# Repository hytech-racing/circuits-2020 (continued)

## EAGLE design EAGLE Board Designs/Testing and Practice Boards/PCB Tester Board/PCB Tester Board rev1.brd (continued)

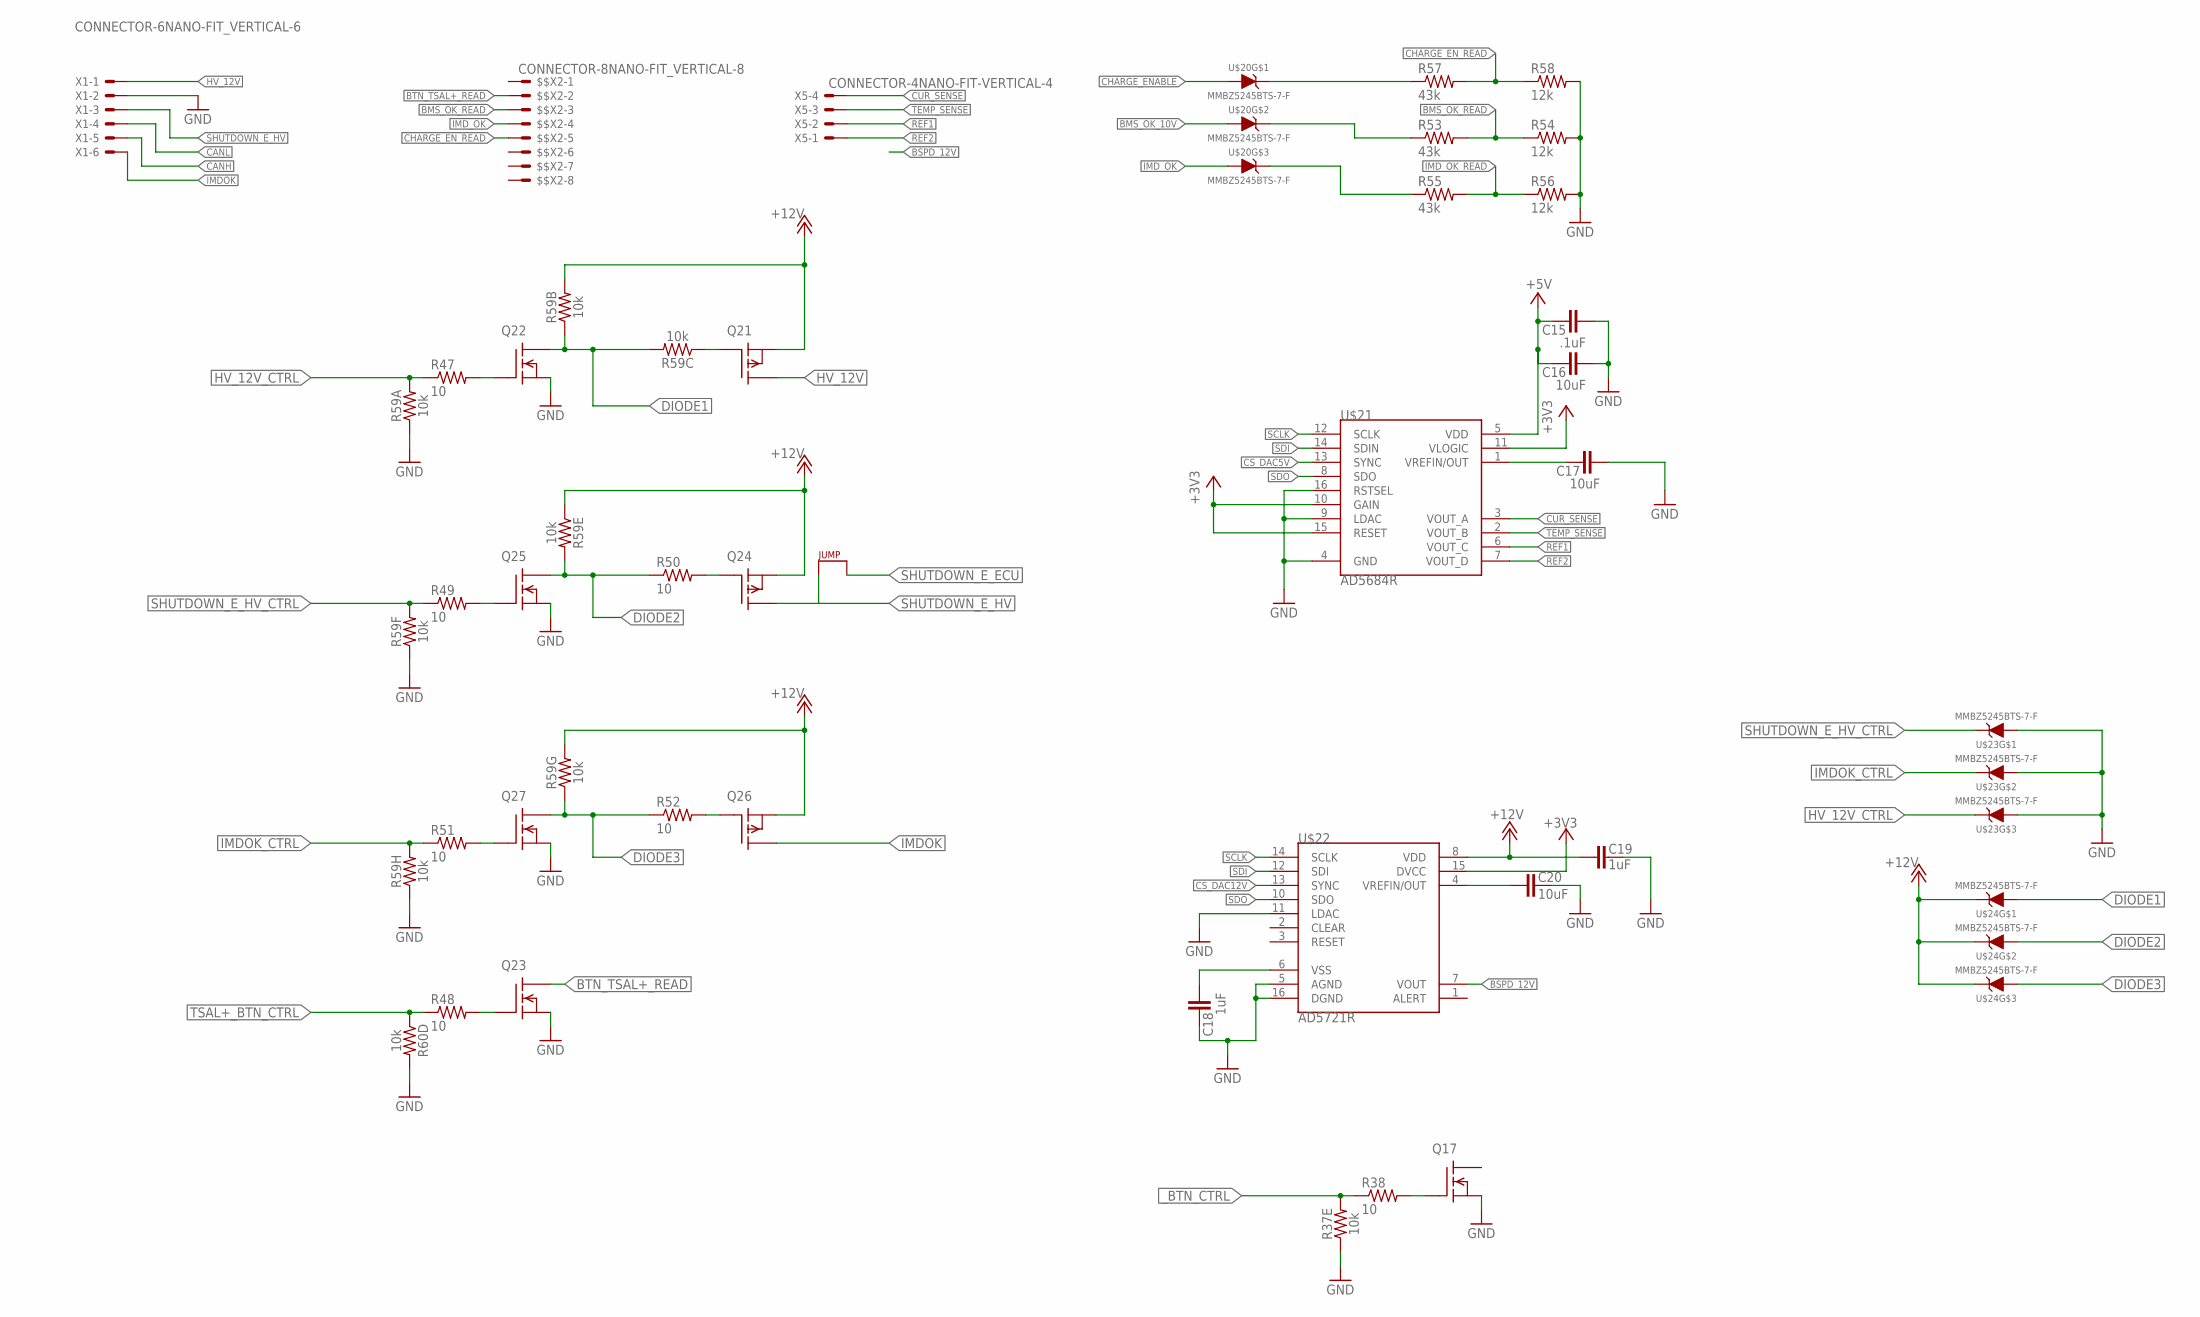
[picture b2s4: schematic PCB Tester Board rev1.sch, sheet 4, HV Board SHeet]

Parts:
$$X2: CONNECTOR-8NANO-FIT_VERTICAL-8; NANO-FIT_VERTICAL-8
C15: .1uF; 0603-CAP
C16, C17, C20: 10uF; 0603-CAP
C18, C19: 1uF; 0603-CAP
J1: JUMPER.1; 1X02
Q17, Q22, Q23, Q25, Q27: DMG3406LSOT; SOT23
Q21, Q24, Q26: P-CHANNEL_MOSFET_DMP3099L-7; SOT23
R37, R59, R60: 10k; YAG_YC248-M
R38, R47, R48, R49, R50, R51, R52: 10; 0603-RES
R53, R55, R57: 43k; 0603-RES
R54, R56, R58: 12k; 0603-RES
U$20, U$23, U$24: MMBZ5245BTS-7-F; SOT363
U$21: AD5684R; TSSOP-16
U$22: AD5721R; TSSOP-16
X1: CONNECTOR-6NANO-FIT_VERTICAL-6; NANO-FIT_VERTICAL-6
X5: CONNECTOR-4NANO-FIT-VERTICAL-4; NANO-FIT_VERTICAL-4

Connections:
+3V3: U$21.10 (GAIN), U$21.11 (VLOGIC), U$21.15 (RESET), U$22.15 (DVCC); also elsewhere on the board
+5V: C15.1, C16.1, U$21.5 (VDD); also elsewhere on the board
+12V: C19.2, Q21.2 (S), Q24.2 (S), Q26.2 (S), R59.5 (1), R59.10 (2), R59.15 (2), U$22.8 (VDD), U$24.P$4 (C), U$24.P$5 (C), U$24.P$6 (C); also elsewhere on the board
BMS_OK_10V: U$20.P$2 (A)
BMS_OK_READ: R53.2, R54.1
BSPD_12V: U$22.7 (VOUT)
BTN_TSAL+_READ: $$X2.P$2, Q23.3 (D)
CANH: X1.P$5; also elsewhere on the board
CANL: X1.P$4; also elsewhere on the board
CHARGE_ENABLE: U$20.P$1 (A)
CHARGE_EN_READ: R57.2, R58.1
CS_DAC5V: U$21.13 (SYNC); also elsewhere on the board
CS_DAC12V: U$22.13 (SYNC); also elsewhere on the board
CUR_SENSE: U$21.3 (VOUT_A), X5.P$4
DIODE1: Q22.3 (D), R59.2 (1), R59.14 (2), U$24.P$1 (A)
DIODE2: Q25.3 (D), R50.1, R59.12 (2), U$24.P$2 (A)
DIODE3: Q27.3 (D), R52.1, R59.7 (1), U$24.P$3 (A)
GND: C15.2, C16.2, C17.2, C18.1, C19.1, C20.1, Q17.2 (S), Q22.2 (S), Q23.2 (S), Q25.2 (S), Q27.2 (S), R37.5 (1), R54.2, R56.2, R58.2, R59.1, R59.6 (1), R59.8 (1), R60.13 (2), U$21.4 (GND), U$21.9 (LDAC), U$21.16 (RSTSEL), U$22.5 (AGND), U$22.11 (LDAC), U$22.16 (DGND), U$23.P$1 (A), U$23.P$2 (A), U$23.P$3 (A), X1.P$2; also elsewhere on the board
HV_12V: Q21.3 (D), X1.P$1
HV_12V_CTRL: R47.1, R59.16 (2), U$23.P$6 (C)
IMDOK: Q26.3 (D), X1.P$6
IMDOK_CTRL: R51.1, R59.9 (2), U$23.P$5 (C)
IMD_OK: U$20.P$3 (A)
IMD_OK_READ: R55.2, R56.1
unnamed: Q17.1 (G), R38.2
unnamed: Q22.1 (G), R47.2
unnamed: Q21.1 (G), R59.3 (1)
unnamed: Q23.1 (G), R48.2
unnamed: Q25.1 (G), R49.2
unnamed: Q24.1 (G), R50.2
unnamed: Q27.1 (G), R51.2
unnamed: Q26.1 (G), R52.2
unnamed: R57.1, U$20.P$4 (C)
unnamed: R53.1, U$20.P$5 (C)
unnamed: R55.1, U$20.P$6 (C)
unnamed: C17.1, U$21.1 (VREFIN/OUT)
unnamed: C20.2, U$22.4 (VREFIN/OUT)
unnamed: C18.2, U$22.6 (VSS)
REF1: U$21.6 (VOUT_C), X5.P$2
REF2: U$21.7 (VOUT_D), X5.P$1
SCLK: U$21.12 (SCLK), U$22.14 (SCLK); also elsewhere on the board
SDI: U$21.14 (SDIN), U$22.12 (SDI); also elsewhere on the board
SDO: U$21.8 (SDO), U$22.10 (SDO); also elsewhere on the board
SHUTDOWN_E_ECU: J1.2
SHUTDOWN_E_HV: Q24.3 (D), X1.P$3
SHUTDOWN_E_HV_CTRL: R49.1, R59.11 (2)
SSOK1: J1.1
TEMP_SENSE: U$21.2 (VOUT_B), X5.P$3
TSAL+_BTN_CTRL: R48.1, R60.4 (1)
_BTN_CTRL: R37.12 (2), R38.1

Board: 2 copper layers, 194 parts (0 on the bottom side), 147 nets, no tracks yet.

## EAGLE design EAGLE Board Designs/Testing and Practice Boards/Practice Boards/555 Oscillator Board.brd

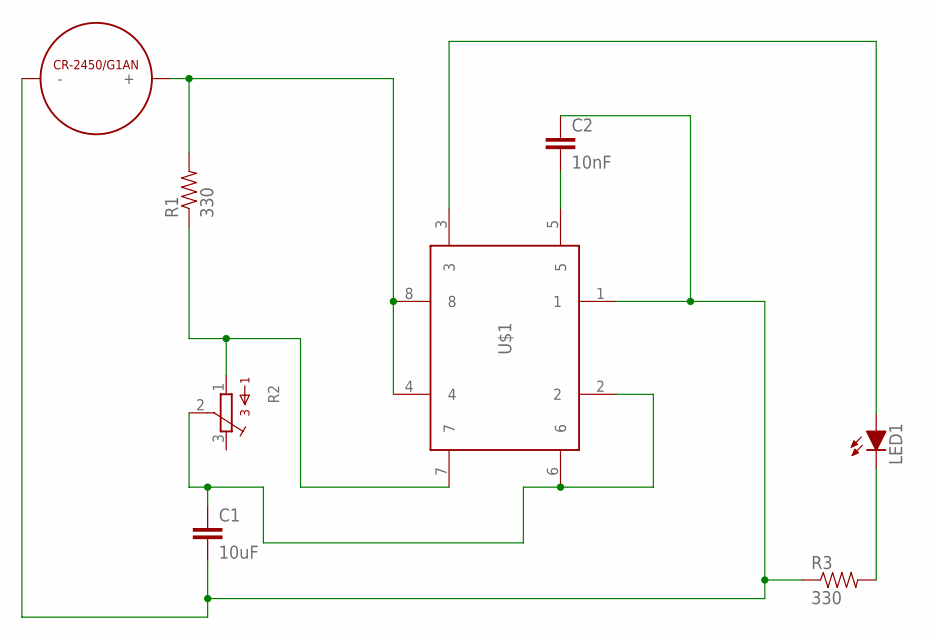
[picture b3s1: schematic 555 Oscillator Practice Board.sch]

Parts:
C1: 10uF; AXIAL-5MM
C2: 10nF; AXIAL-5MM
LED1: LED-5MM
R1, R3: 330; AXIAL-0.3
R2: TRIMPOT_3296C; TRIMPOT_3296
U$1: 555_TIMER; DIL08
U$2: CR-2450/G1AN

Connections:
unnamed: C1.P$2 (2), C2.P$1 (1), R3.P$1 (1), U$1.1, U$2.-
unnamed: R1.P$1 (1), R2.1, U$1.7
unnamed: R1.P$2 (2), U$1.4, U$1.8, U$2.+_0 (+), U$2.+_1 (+)
unnamed: LED1.A, U$1.3
unnamed: LED1.K (C), R3.P$2 (2)
unnamed: C2.P$2 (2), U$1.5
unnamed: C1.P$1 (1), R2.2, U$1.2, U$1.6

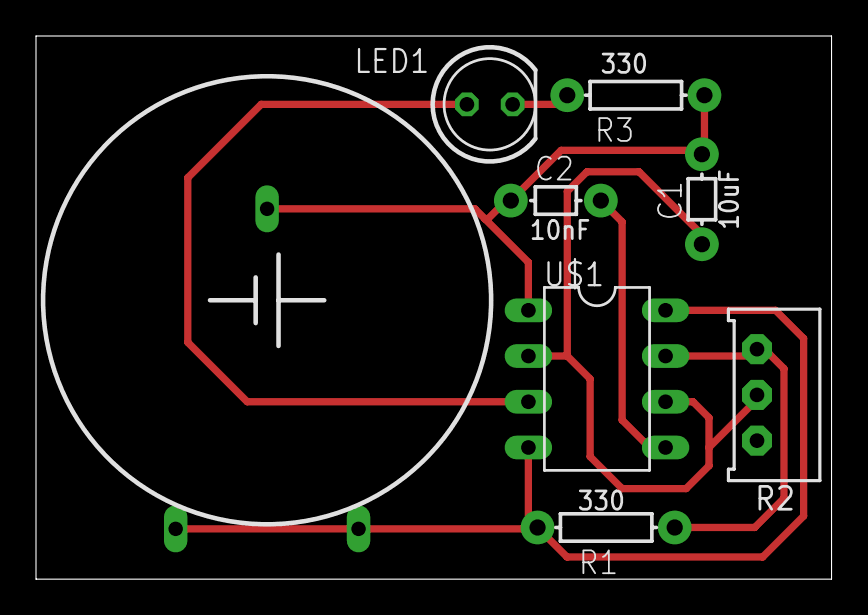
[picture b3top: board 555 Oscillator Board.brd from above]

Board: 2 copper layers, 44.2 x 30.2 mm, 8 parts (0 on the bottom side), 7 nets.

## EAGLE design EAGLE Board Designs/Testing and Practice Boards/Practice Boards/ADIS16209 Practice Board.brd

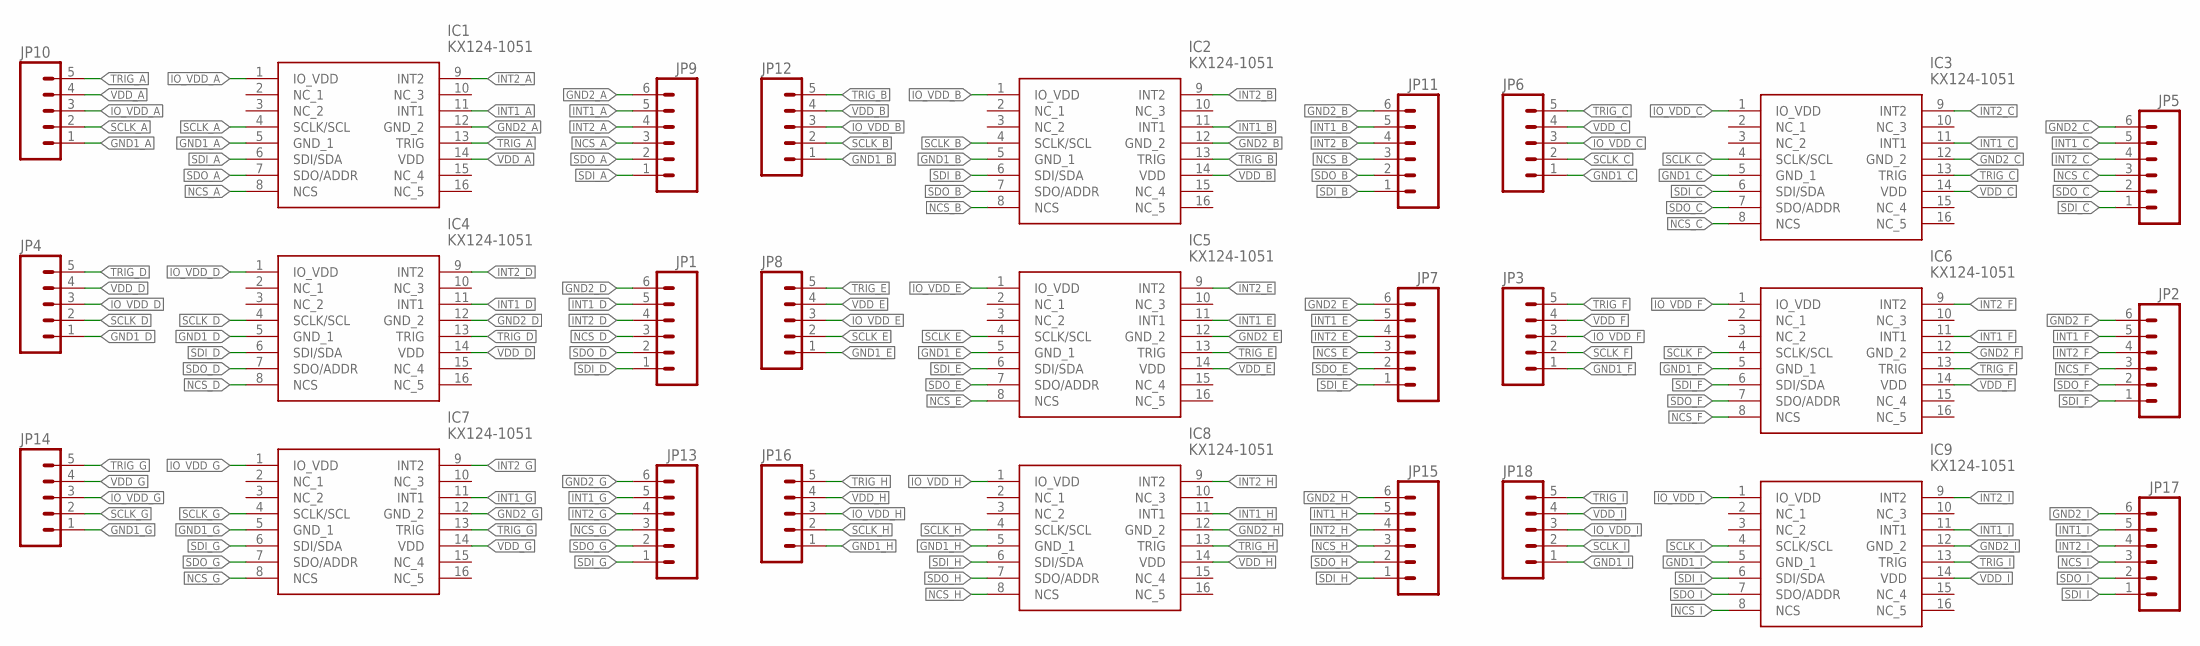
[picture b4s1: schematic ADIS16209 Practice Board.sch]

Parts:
IC1, IC2, IC3, IC4, IC5, IC6, IC7, IC8, IC9: KX124-1051; 3X3LGA
JP1, JP2, JP5, JP7, JP9, JP11, JP13, JP15, JP17: M06; 1X06
JP3, JP4, JP6, JP8, JP10, JP12, JP14, JP16, JP18: M05; 1X05

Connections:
GND1_A: IC1.5 (GND_1), JP10.1
GND1_B: IC2.5 (GND_1), JP12.1
GND1_C: IC3.5 (GND_1), JP6.1
GND1_D: IC4.5 (GND_1), JP4.1
GND1_E: IC5.5 (GND_1), JP8.1
GND1_F: IC6.5 (GND_1), JP3.1
GND1_G: IC7.5 (GND_1), JP14.1
GND1_H: IC8.5 (GND_1), JP16.1
GND1_I: IC9.5 (GND_1), JP18.1
GND2_A: IC1.12 (GND_2), JP9.6
GND2_B: IC2.12 (GND_2), JP11.6
GND2_C: IC3.12 (GND_2), JP5.6
GND2_D: IC4.12 (GND_2), JP1.6
GND2_E: IC5.12 (GND_2), JP7.6
GND2_F: IC6.12 (GND_2), JP2.6
GND2_G: IC7.12 (GND_2), JP13.6
GND2_H: IC8.12 (GND_2), JP15.6
GND2_I: IC9.12 (GND_2), JP17.6
INT1_A: IC1.11 (INT1), JP9.5
INT1_B: IC2.11 (INT1), JP11.5
INT1_C: IC3.11 (INT1), JP5.5
INT1_D: IC4.11 (INT1), JP1.5
INT1_E: IC5.11 (INT1), JP7.5
INT1_F: IC6.11 (INT1), JP2.5
INT1_G: IC7.11 (INT1), JP13.5
INT1_H: IC8.11 (INT1), JP15.5
INT1_I: IC9.11 (INT1), JP17.5
INT2_A: IC1.9 (INT2), JP9.4
INT2_B: IC2.9 (INT2), JP11.4
INT2_C: IC3.9 (INT2), JP5.4
INT2_D: IC4.9 (INT2), JP1.4
INT2_E: IC5.9 (INT2), JP7.4
INT2_F: IC6.9 (INT2), JP2.4
INT2_G: IC7.9 (INT2), JP13.4
INT2_H: IC8.9 (INT2), JP15.4
INT2_I: IC9.9 (INT2), JP17.4
IO_VDD_A: IC1.1 (IO_VDD), JP10.3
IO_VDD_B: IC2.1 (IO_VDD), JP12.3
IO_VDD_C: IC3.1 (IO_VDD), JP6.3
IO_VDD_D: IC4.1 (IO_VDD), JP4.3
IO_VDD_E: IC5.1 (IO_VDD), JP8.3
IO_VDD_F: IC6.1 (IO_VDD), JP3.3
IO_VDD_G: IC7.1 (IO_VDD), JP14.3
IO_VDD_H: IC8.1 (IO_VDD), JP16.3
IO_VDD_I: IC9.1 (IO_VDD), JP18.3
NCS_A: IC1.8 (NCS), JP9.3
NCS_B: IC2.8 (NCS), JP11.3
NCS_C: IC3.8 (NCS), JP5.3
NCS_D: IC4.8 (NCS), JP1.3
NCS_E: IC5.8 (NCS), JP7.3
NCS_F: IC6.8 (NCS), JP2.3
NCS_G: IC7.8 (NCS), JP13.3
NCS_H: IC8.8 (NCS), JP15.3
NCS_I: IC9.8 (NCS), JP17.3
SCLK_A: IC1.4 (SCLK/SCL), JP10.2
SCLK_B: IC2.4 (SCLK/SCL), JP12.2
SCLK_C: IC3.4 (SCLK/SCL), JP6.2
SCLK_D: IC4.4 (SCLK/SCL), JP4.2
SCLK_E: IC5.4 (SCLK/SCL), JP8.2
SCLK_F: IC6.4 (SCLK/SCL), JP3.2
SCLK_G: IC7.4 (SCLK/SCL), JP14.2
SCLK_H: IC8.4 (SCLK/SCL), JP16.2
SCLK_I: IC9.4 (SCLK/SCL), JP18.2
SDI_A: IC1.6 (SDI/SDA), JP9.1
SDI_B: IC2.6 (SDI/SDA), JP11.1
SDI_C: IC3.6 (SDI/SDA), JP5.1
SDI_D: IC4.6 (SDI/SDA), JP1.1
SDI_E: IC5.6 (SDI/SDA), JP7.1
SDI_F: IC6.6 (SDI/SDA), JP2.1
SDI_G: IC7.6 (SDI/SDA), JP13.1
SDI_H: IC8.6 (SDI/SDA), JP15.1
SDI_I: IC9.6 (SDI/SDA), JP17.1
SDO_A: IC1.7 (SDO/ADDR), JP9.2
SDO_B: IC2.7 (SDO/ADDR), JP11.2
SDO_C: IC3.7 (SDO/ADDR), JP5.2
SDO_D: IC4.7 (SDO/ADDR), JP1.2
SDO_E: IC5.7 (SDO/ADDR), JP7.2
SDO_F: IC6.7 (SDO/ADDR), JP2.2
SDO_G: IC7.7 (SDO/ADDR), JP13.2
SDO_H: IC8.7 (SDO/ADDR), JP15.2
SDO_I: IC9.7 (SDO/ADDR), JP17.2
TRIG_A: IC1.13 (TRIG), JP10.5
TRIG_B: IC2.13 (TRIG), JP12.5
TRIG_C: IC3.13 (TRIG), JP6.5
TRIG_D: IC4.13 (TRIG), JP4.5
TRIG_E: IC5.13 (TRIG), JP8.5
TRIG_F: IC6.13 (TRIG), JP3.5
TRIG_G: IC7.13 (TRIG), JP14.5
TRIG_H: IC8.13 (TRIG), JP16.5
TRIG_I: IC9.13 (TRIG), JP18.5
VDD_A: IC1.14 (VDD), JP10.4
VDD_B: IC2.14 (VDD), JP12.4
VDD_C: IC3.14 (VDD), JP6.4
VDD_D: IC4.14 (VDD), JP4.4
VDD_E: IC5.14 (VDD), JP8.4
VDD_F: IC6.14 (VDD), JP3.4
VDD_G: IC7.14 (VDD), JP14.4
VDD_H: IC8.14 (VDD), JP16.4
VDD_I: IC9.14 (VDD), JP18.4

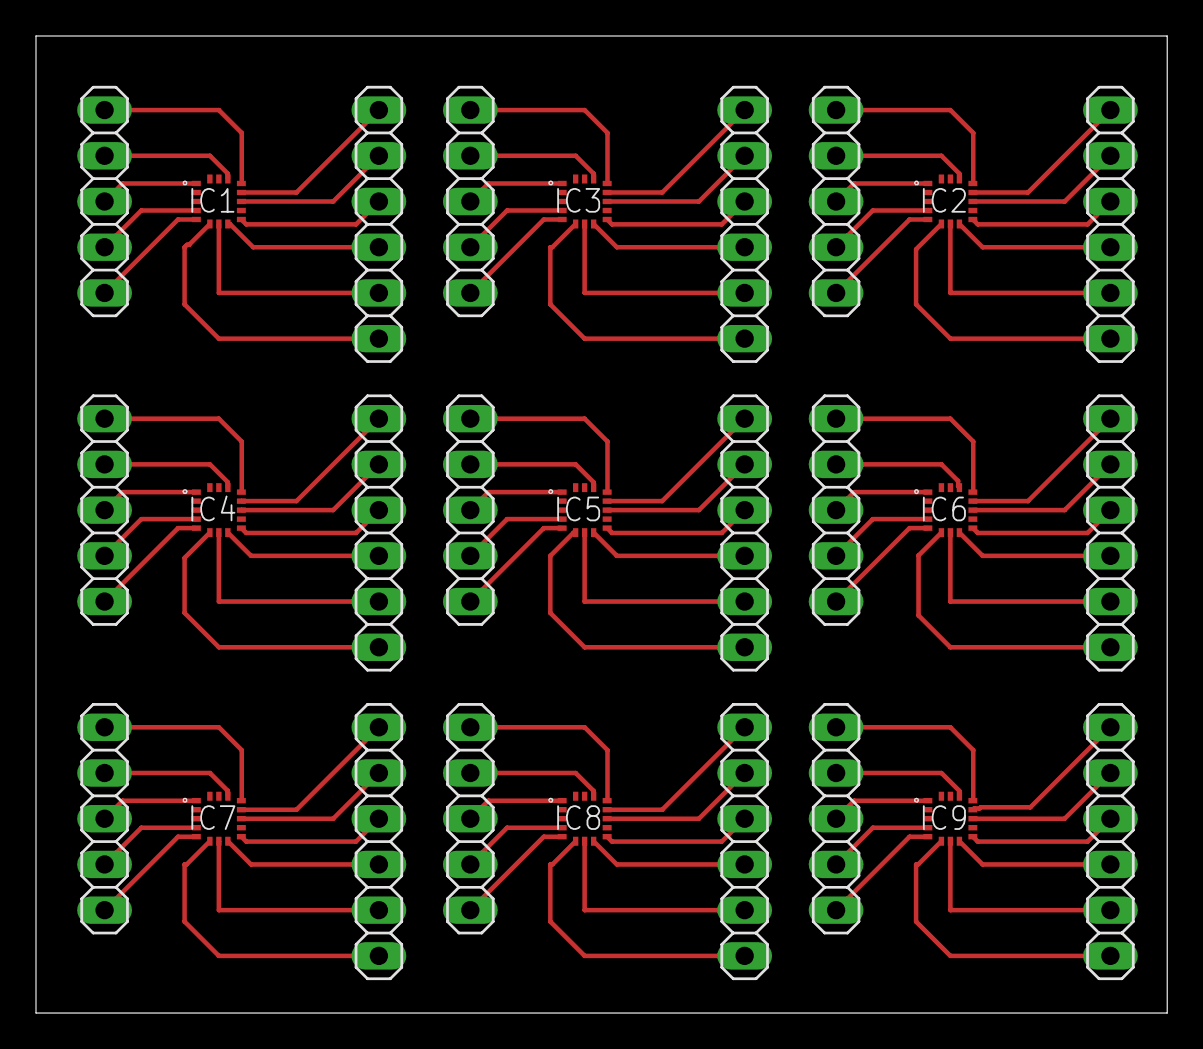
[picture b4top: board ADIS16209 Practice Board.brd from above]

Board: 2 copper layers, 62.8 x 54.3 mm, 27 parts (0 on the bottom side), 99 nets.
